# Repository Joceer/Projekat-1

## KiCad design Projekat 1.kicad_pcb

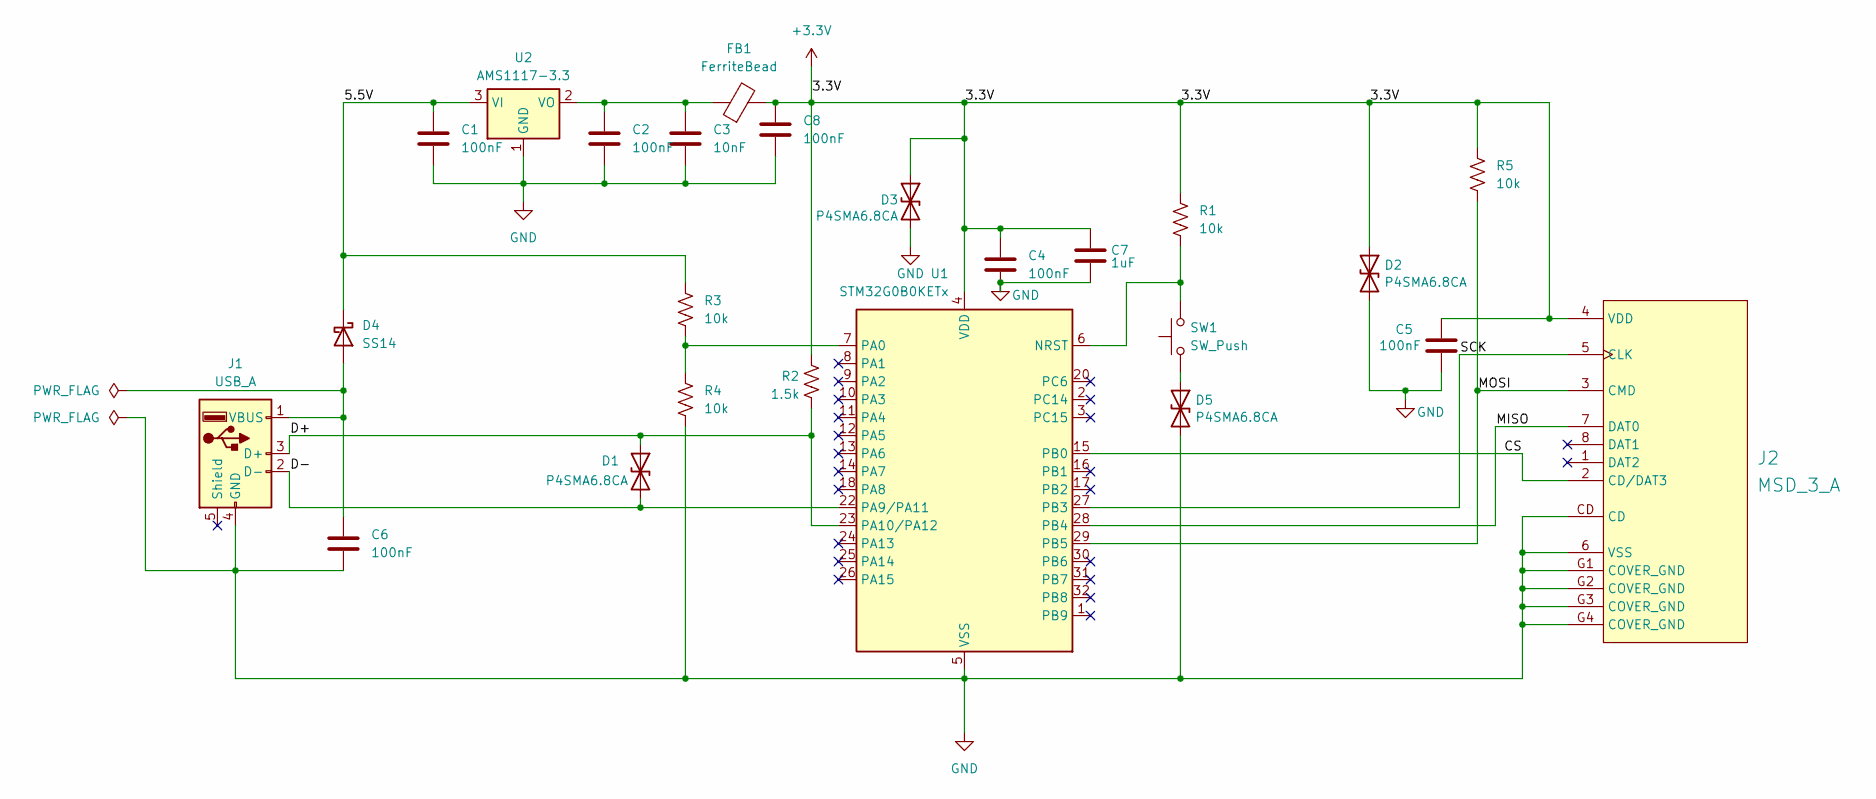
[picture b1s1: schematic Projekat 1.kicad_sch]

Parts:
C1, C2, C4, C5, C6, C8: 100nF; C_0805_2012Metric
C3: 10nF; C_0805_2012Metric
C7: 1uF; CP_Radial_Tantal_D4.5mm_P2.50mm
D1, D2, D3, D5: P4SMA6.8CA; D_SMA; Farnell 2762977
D4: SS14; D_SMA
FB1: FerriteBead; LairdTech_28C0236-0JW-10
J1: USB_A; USB_A_TE_292303-7_Horizontal
J2: MSD_3_A; CUI_MSD-3-A
R1, R3, R4, R5: 10k; R_0805_2012Metric
R2: 1.5k; R_0805_2012Metric
SW1: SW_Push; SW_SPST_FSMSM
U1: STM32G0B0KETx; LQFP-32_7x7mm_P0.8mm
U2: AMS1117-3.3; SOT-223-3_TabPin2

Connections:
+3.3V: C4.1, C5.1, C7.1, C8.1, D2.1 (A1), D3.1 (A1), FB1.2, J2.4 (VDD), R1.1, R2.1, R5.1, U1.4 (VDD)
/5.5V: C1.1, D4.1 (K), R3.1, U2.3 (VI)
/CS: J2.2 (CD/DAT3), U1.15 (PB0)
/D+: D1.1 (A1), J1.3 (D+), R2.2, U1.23 (PA10/PA12)
/D-: D1.2 (A2), J1.2 (D-), U1.22 (PA9/PA11)
/MISO: J2.7 (DAT0), U1.28 (PB4)
/MOSI: J2.3 (CMD), R5.2, U1.29 (PB5)
/SCK: J2.5 (CLK), U1.27 (PB3)
GND: C1.2, C2.2, C3.2, C4.2, C5.2, C6.2, C7.2, C8.2, D2.2 (A2), D3.2 (A2), D5.2 (A2), J1.4 (GND), J2.6 (VSS), J2.CD, J2.G1 (COVER_GND), J2.G2 (COVER_GND), J2.G3 (COVER_GND), J2.G4 (COVER_GND), R4.2, U1.5 (VSS), U2.1 (GND)
unnamed: C6.1, D4.2 (A), J1.1 (VBUS)
unnamed: D5.1 (A1), SW1.1
unnamed: R1.2, SW1.2, U1.6 (NRST)
unnamed: R3.2, R4.1, U1.7 (PA0)
unnamed: C2.1, C3.1, FB1.1, U2.2 (VO)

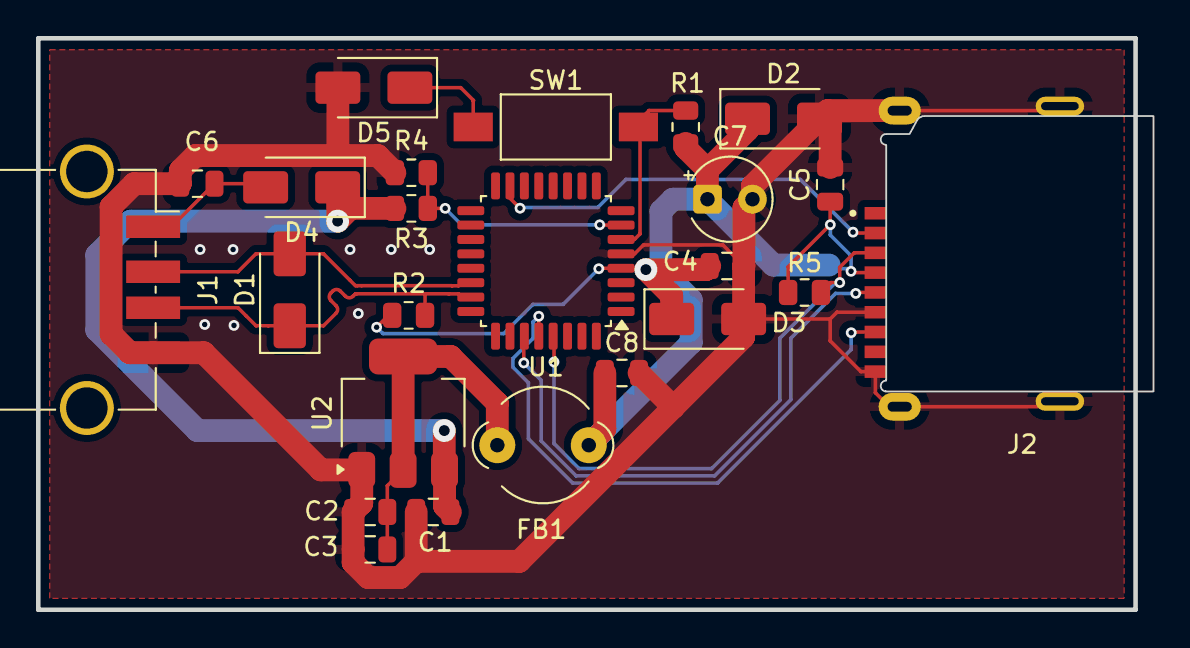
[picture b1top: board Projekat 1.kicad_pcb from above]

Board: 2 copper layers, 61.9 x 31.8 mm, 24 parts (0 on the bottom side), 14 nets.

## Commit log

2025-07-31 Početak
